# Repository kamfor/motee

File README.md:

# motee_v3
Highly integrated actuator for robotics

### Components
* Pololu micro DC HP motor
* Magnetic encoder
* STM32  MCU
* TI high current H bridge
* RS485 controller 
* Logic Level converter 
* Current sensor

### Features
* Multi Master communication
* Easy commands
* Expansibility
* Arduino, Rbpi, AVR, ARM, PIC, PC compatibility 
* Task controlled
* High torque 
* ...

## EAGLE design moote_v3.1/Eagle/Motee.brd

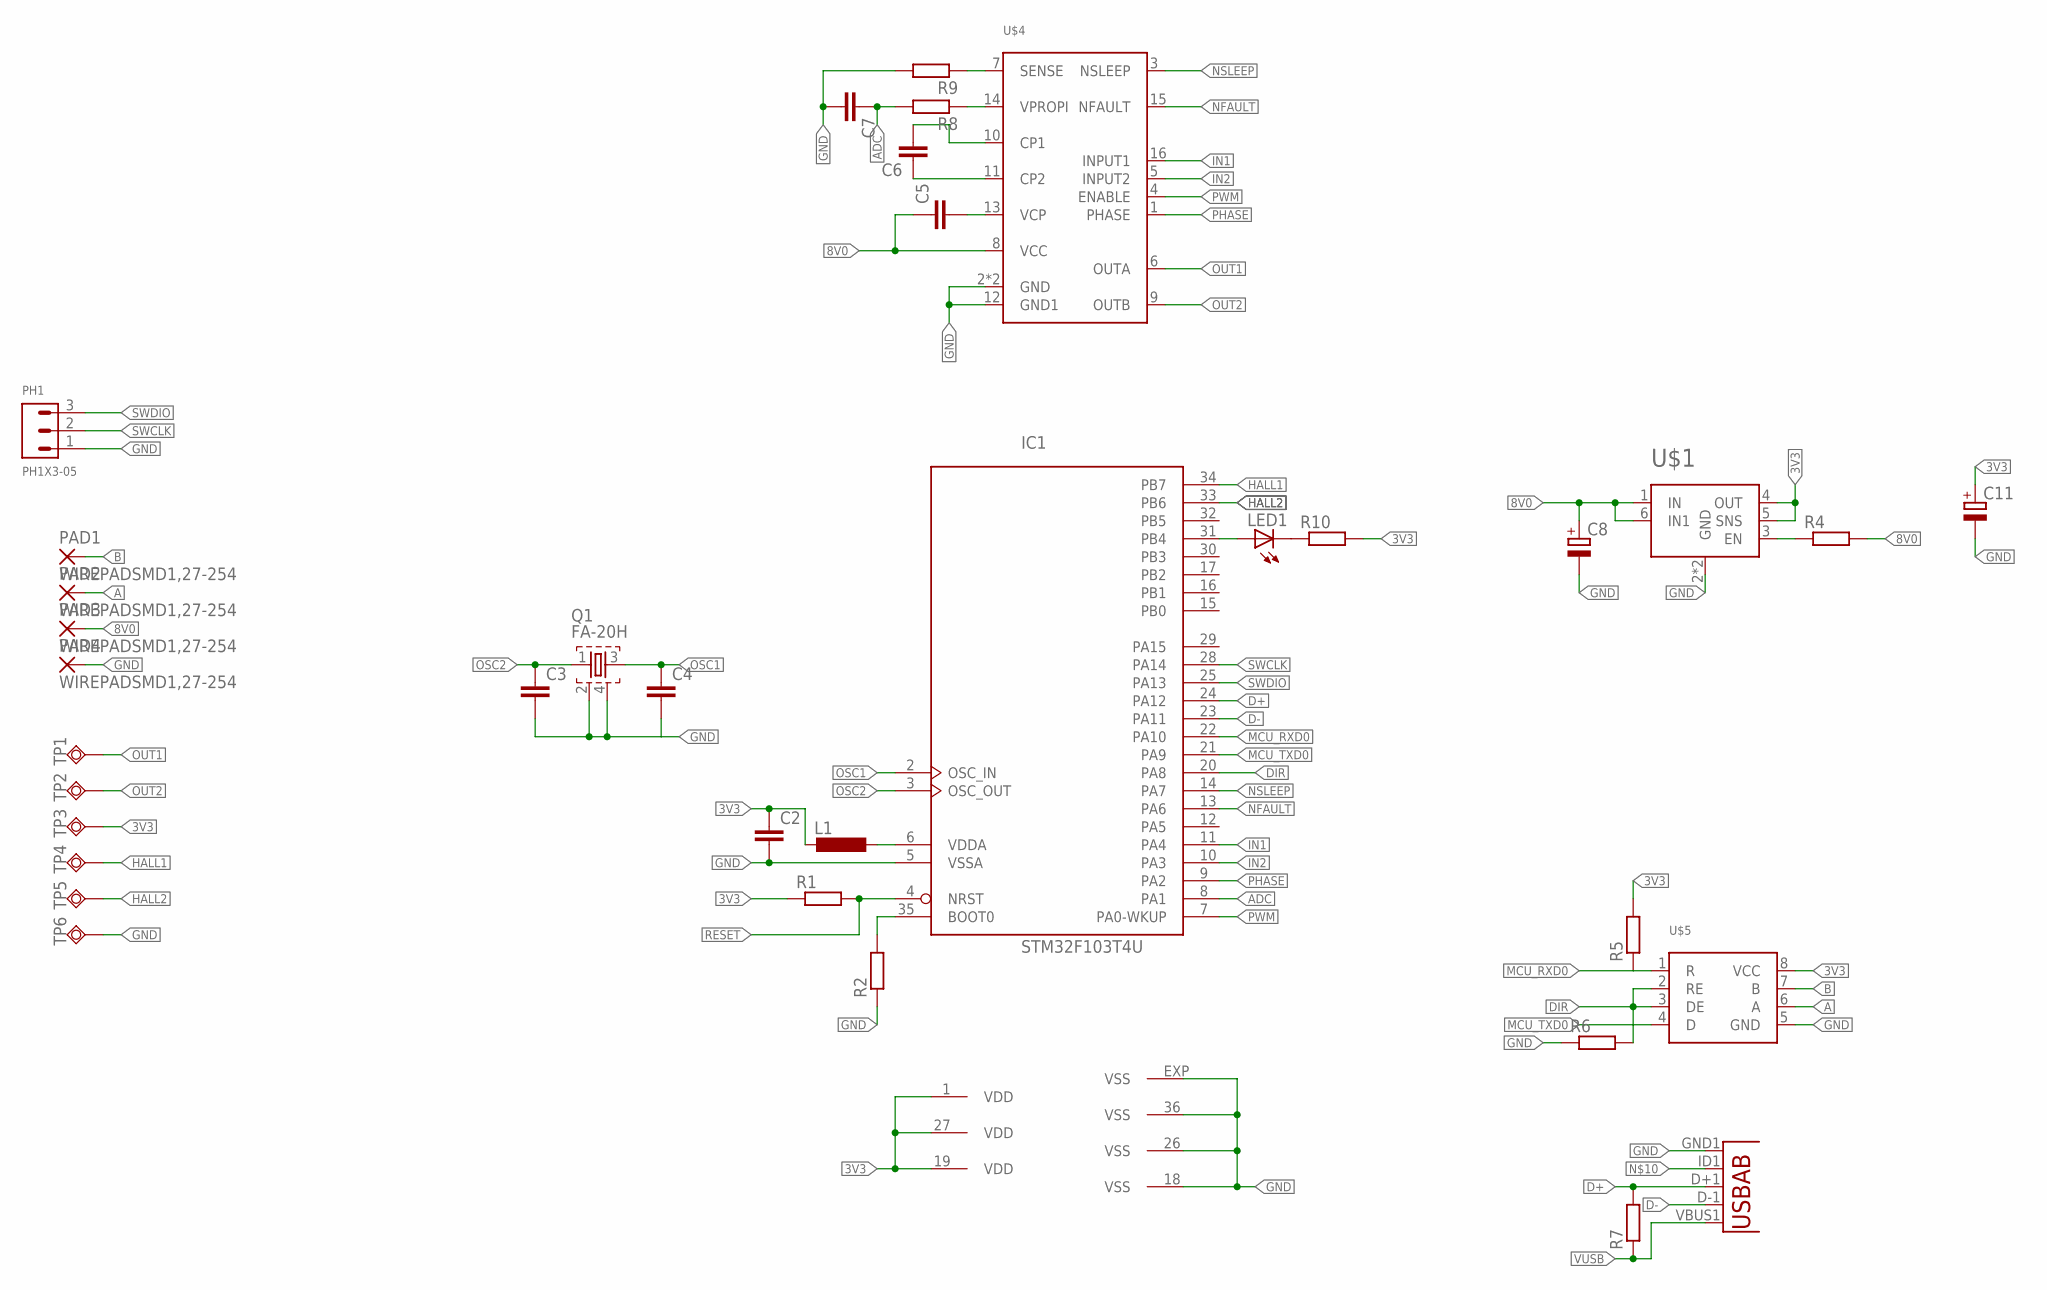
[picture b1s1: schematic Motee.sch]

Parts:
C2, C3, C4, C5, C6, C7: C-EUC0402K; C0402K
C8, C11: CPOL-EUB/3528-21R; B/3528-21R
IC1: STM32F103T4U; VFQFPN36
L1: L-EUL2012C; L2012C
LED1: LEDCHIP-LED0603; CHIP-LED0603
PAD1, PAD2, PAD3, PAD4: WIREPADSMD1,27-254; SMD1,27-2,54
PH1: PH1X3-05; PH005-1-3
Q1: FA-20H
R1, R2, R4, R5, R6, R7, R8, R9, R10: R-EU_R0402; R0402
TP1, TP2, TP3, TP4, TP5, TP6: TPSQTP20SQ; TP20SQ
U1: USB""; USB-MICRO-SMD
U$1: LP38693
U$4: DRV8801; WQFN-16
U$5: MAX22501EATA; TDFN-8

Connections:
3V3: C2.1, C11.+, IC1.1 (VDD), IC1.19 (VDD), IC1.27 (VDD), L1.2, R1.1, R5.2, R10.2, TP3.TP, U$1.4 (OUT), U$1.5 (SNS), U$5.8 (VCC)
8V0: C5.1, C8.+, PAD3.1, R4.2, U$1.1 (IN), U$1.6 (IN1), U$4.8 (VCC)
A: PAD2.1, U$5.6 (A)
ADC: C7.1, IC1.8 (PA1), R8.2
B: PAD1.1, U$5.7 (B)
D+: IC1.24 (PA12), R7.2, U1.D+1 (D+)
D-: IC1.23 (PA11), U1.D-1 (D-)
DIR: IC1.20 (PA8), R6.2, U$5.2 (RE), U$5.3 (DE)
GND: C2.2, C3.2, C4.2, C7.2, C8.-, C11.-, IC1.5 (VSSA), IC1.18 (VSS), IC1.26 (VSS), IC1.36 (VSS), IC1.EXP (VSS), PAD4.1, PH1.1, Q1.2, Q1.4, R2.1, R6.1, R9.2, TP6.TP, U1.GND1 (GND), U$1.2 (GND), U$1.7 (GND), U$4.2 (GND), U$4.12 (GND1), U$4.17 (GND), U$5.5 (GND)
HALL1: IC1.34 (PB7), TP4.TP
HALL2: IC1.33 (PB6), TP5.TP
IN1: IC1.11 (PA4), U$4.16 (INPUT1)
IN2: IC1.10 (PA3), U$4.5 (INPUT2)
MCU_RXD0: IC1.22 (PA10), R5.1, U$5.1 (R)
MCU_TXD0: IC1.21 (PA9), U$5.4 (D)
unnamed: IC1.35 (BOOT0), R2.2
unnamed: IC1.6 (VDDA), L1.1
unnamed: C6.1, U$4.11 (CP2)
unnamed: C5.2, U$4.13 (VCP)
unnamed: C6.2, U$4.10 (CP1)
unnamed: R4.1, U$1.3 (EN)
unnamed: R8.1, U$4.14 (VPROPI)
unnamed: R9.1, U$4.7 (SENSE)
unnamed: LED1.C, R10.1
unnamed: IC1.31 (PB4), LED1.A
NFAULT: IC1.13 (PA6), U$4.15 (NFAULT)
NSLEEP: IC1.14 (PA7), U$4.3 (NSLEEP)
OSC1: C4.1, IC1.2 (OSC_IN), Q1.3
OSC2: C3.1, IC1.3 (OSC_OUT), Q1.1
OUT1: TP1.TP, U$4.6 (OUTA)
OUT2: TP2.TP, U$4.9 (OUTB)
PHASE: IC1.9 (PA2), U$4.1 (PHASE)
PWM: IC1.7 (PA0-WKUP), U$4.4 (ENABLE)
RESET: IC1.4 (NRST), R1.2
SWCLK: IC1.28 (PA14), PH1.2
SWDIO: IC1.25 (PA13), PH1.3
VUSB: R7.1, U1.VBUS1 (VBUS)

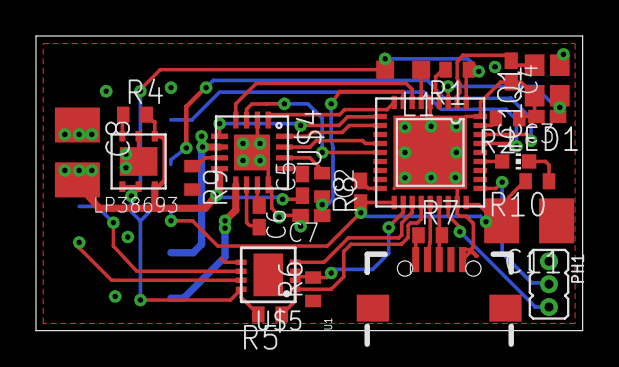
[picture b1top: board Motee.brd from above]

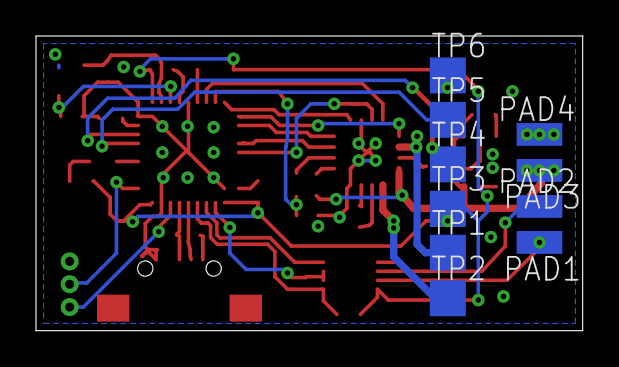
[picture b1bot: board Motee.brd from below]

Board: 2 copper layers, 30.4 x 16.4 mm, 36 parts (10 on the bottom side), 37 nets.

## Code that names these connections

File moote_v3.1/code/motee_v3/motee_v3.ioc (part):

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Mcu.Name=STM32F103T(8-B)Ux
Mcu.Package=VFQFPN36
Mcu.UserName=STM32F103T8Ux
PA0-WKUP.Signal=S_TIM2_CH1_ETR
PA1.GPIOParameters=GPIO_Label
PA1.GPIO_Label=MOTOR_CURRENT
PA1.Signal=ADCx_IN1
PA10.Mode=Asynchronous
PA10.Signal=USART1_RX
PA11.Mode=Device
PA11.Signal=USB_DM
PA12.Mode=Device
PA12.Signal=USB_DP
PA13.Mode=Serial_Wire
PA13.Signal=SYS_JTMS-SWDIO
PA14.Mode=Serial_Wire
PA14.Signal=SYS_JTCK-SWCLK
PA2.GPIOParameters=GPIO_Label
PA2.GPIO_Label=MOTOR_PHASE
PA2.Signal=GPIO_Output
PA3.GPIOParameters=GPIO_Speed,GPIO_Label
PA3.GPIO_Label=MOTOR_MODE2
PA3.GPIO_Speed=GPIO_SPEED_FREQ_HIGH
PA3.Signal=GPIO_Output
PA4.GPIOParameters=GPIO_Speed,GPIO_Label
PA4.GPIO_Label=MOTOR_MODE1
PA4.GPIO_Speed=GPIO_SPEED_FREQ_HIGH
PA4.Signal=GPIO_Output
PA6.GPIOParameters=GPIO_PuPd,GPIO_Label
PA6.GPIO_Label=MOTOR_FAULT
PA6.GPIO_PuPd=GPIO_PULLUP
PA6.Signal=GPIO_Input
PA7.GPIOParameters=PinState,GPIO_Label,GPIO_ModeDefaultOutputPP
PA7.GPIO_Label=MOTOR_SLEEP
PA7.GPIO_ModeDefaultOutputPP=GPIO_MODE_OUTPUT_PP
PA7.PinState=GPIO_PIN_SET
PA7.Signal=GPIO_Output
PA8.GPIOParameters=GPIO_Label
PA8.GPIO_Label=RS485_DIR
PA8.Signal=GPIO_Output
PA9.Mode=Asynchronous
PA9.Signal=USART1_TX
PB4.GPIOParameters=GPIO_Label
PB4.GPIO_Label=USER_LED
PB4.Signal=GPIO_Output
PB6.GPIOParameters=GPIO_PuPd
PB6.GPIO_PuPd=GPIO_PULLUP
PB6.Signal=S_TIM4_CH1
PB7.GPIOParameters=GPIO_PuPd
PB7.GPIO_PuPd=GPIO_PULLUP
PB7.Signal=S_TIM4_CH2
PD0-OSC_IN.Mode=HSE-External-Oscillator
PD0-OSC_IN.Signal=RCC_OSC_IN
PD1-OSC_OUT.Mode=HSE-External-Oscillator
PD1-OSC_OUT.Signal=RCC_OSC_OUT
RCC.HSEDivPLL=RCC_HSE_PREDIV_DIV2
RCC.HSE_VALUE=16000000
RCC.SYSCLKFreq_VALUE=72000000
RCC.SYSCLKSource=RCC_SYSCLKSOURCE_PLLCLK
board=motee_v3

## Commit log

2016-02-11 Update README.md
    Few minor changes
2016-02-16 initial commit.
2016-02-16 First sketch of schematic.
2016-02-16 Minor fixes in schematic.
2016-02-17 Encoder has been added.
2016-04-01 test
2016-04-02 blas
2016-04-02 initial
2016-04-20 poprawki
2016-04-30 poprawiona
2016-05-08 gerbery
2016-05-09 gerbery_v2
2016-05-14 makefile
2016-09-11 ver3
2016-09-13 dodane wartosci elementow
2016-09-14 rezystor i dioda 0805
2016-09-29 wylane masy i boot0
2017-01-22 bug fixes
2017-10-23 blinky v3.1
2017-10-26 krzaki hardwarowe
2017-10-29 ADC_current
2017-11-02 encoder works
2017-11-07 simple PID
2017-11-14 hardware bug
2017-11-30 gui layouts
2017-12-10 gui devlist
2017-12-16 usart frame handling
2018-01-07 data plot from nucleo
2018-01-07 motee communication protocol
2018-01-08 rs485 tests
2018-01-10 battery suport
2018-01-15 rs485 works
2018-01-16 pid loop fail
2018-01-19 usb config
2018-01-20 Pid Works
2018-01-21 USB ready to grade
2018-01-21 rs work
2018-01-22 code refactor
2018-06-17 aktualizacja
